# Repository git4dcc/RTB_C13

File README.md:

# RTB_C13

My homebrew RTB C13 track sensor features a 4 channel RailCom® detector, real-time block occupancy monitoring, and dedicated short-circuit protection. It also includes a built-in EDG bus interface, allowing for seamless accessory fan-out and expanded system integration.

<details>
<summary>See also</summary>

- [RTB_C10 - Master](/../../../../git4dcc/RTB_C10)
- [RTB_C11 - Power](/../../../../git4dcc/RTB_C11)
- [RTB_C12 - Booster](/../../../../git4dcc/RTB_C12)

</details>

<details>
<summary>User Guides</summary>

- User Guide - DE
- [User Guide - EN](https://rtb4dcc.de/rtb_user_guide_en/)

</details>

## Track Sensor features
- **HDX**
  - HDX bus (2Mbps half duplex, RS-485 differential)
- **EDG**
  - EDG accessory bus bridge (2Mbps half duplex, TTL level)
- **DCC**
  - Quad-Channel Real-time RailCom® Monitoring and Block Occupancy detection.
  - Current measurement per channel
  - Short-circuit safeguarding for all 4 channels
- **Railcom Detector**
  - channel 1 / channel 2
  - detects unlimited number of decoder per track
  - real-time reporting
- **Current Sensor**
  - 1mA current sensitivity
- firmware update over the bus

# Hardware
The PCB layout uses SMD footprints with 0.4mm pitch, 0603 parts down to 0402. Reflow soldering is mandatory.
The PCB has been optimized for automated assembly (SMD parts are located on bottom side).

## PCB
- 2-layer PCB, FR4, 1.6mm
- CPU: AVR64DB48

## Kicad
[Schematic](doc/C13_schematic.pdf) | [Layout](doc/C13_layout.pdf) | [Gerber](gerber)

# Firmware
Filename structure: { **pcb** }{ **code** }{ **version** }.hex

Example: **C13F0001**.hex

|   | Description |
| --- | --- |
| **pcb** | Name of matching hardware (**C13**) |
| **code** | Type of code contained (**R**=rom, **B**=bootloader, **F**=flash, **U**=bld update, **P**=UPDI factory code) |
| **version** | Release version (**####**) |

[Firmware files](firmware)

## UPDI / Fuses
The fuse settings as well as the P-code (C13Pxxxx.hex) has to be installed by using UPDI.<br>

| Fuses Setting |
| --- |
||

# Images

This project is intended for hobby use only and is distributed in accordance with the Apache License 2.0 agreement.

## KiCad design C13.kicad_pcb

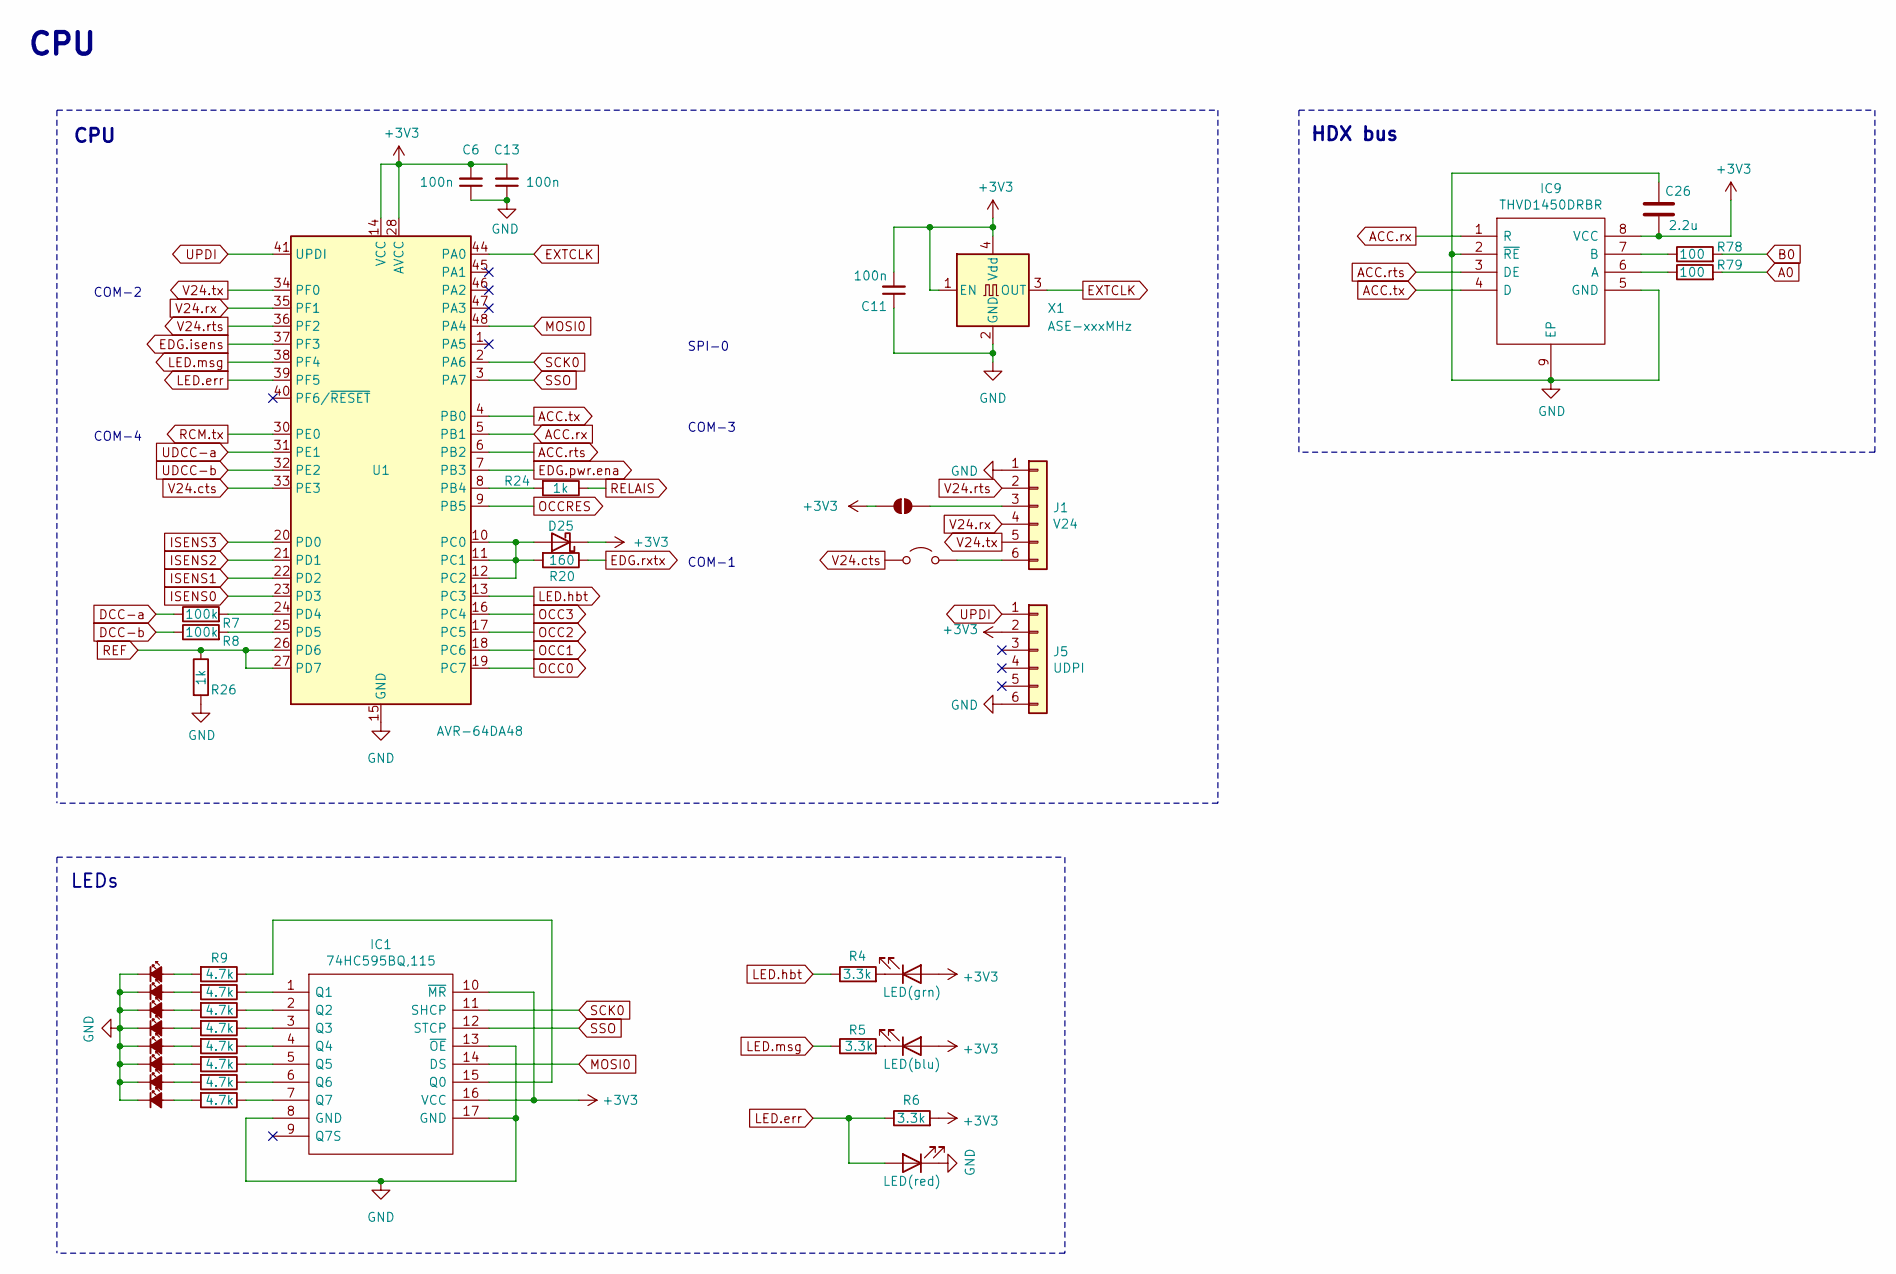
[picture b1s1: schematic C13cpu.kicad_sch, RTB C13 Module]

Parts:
C6, C13: 100n; C_0402_1005Metric; LCSC Part # C307331
C11: 100n; C_0603_1608Metric; LCSC Part # C14663
C26: 2.2u; C_1206_3216Metric; LCSC Part # C50254
D3: LED(grn); LED_0603_1608Metric
D5: LED(blu); LED_0603_1608Metric
D6: LED(red); LED_0603_1608Metric
D7, D8, D9, D10, D11, D12, D13, D14: LED(wht); LED_0603_1608Metric
D25: Schottky; D_0603_1608Metric; LCSC Part # C153761
IC1: 74HC595BQ,115; 74HC595BQ115; Mouser Part Number 771-74HC595BQ-G; LCSC Part # C547123
IC9: THVD1450DRBR; SON65P300X300X100-9N-D; LCSC Part # C1850226
J1: V24; PinHeader_1x06_P2.54mm_Vertical
J5: UDPI; PinHeader_2x03_P1.27mm_Vertical
JP1: SolderJumper_2_Open; SolderJumper-2_P1.3mm_Open_RoundedPad1.0x1.5mm
JP2: Jumper_2_Open; PinHeader_1x02_P2.54mm_Vertical
R4: 3.3k; R_0402_1005Metric; LCSC Part # C25890
R5, R6: 3.3k; R_0603_1608Metric; LCSC Part # C22978
R7, R8: 100k; R_0603_1608Metric; LCSC Part # C25803
R9, R10, R11, R12, R13, R14, R15, R16: 4.7k; R_0603_1608Metric; LCSC Part # C23162
R20: 160; R_0603_1608Metric; LCSC Part # C22808
R24, R26: 1k; R_0402_1005Metric; LCSC Part # C11702
R78, R79: 100; R_1206_3216Metric; LCSC Part # C17901
U1: AVR-64DA48; UQFN-48-1EP_6x6mm_P0.4mm_EP4.62x4.62mm; LCSC Part # C3227372
X1: ASE-xxxMHz; Oscillator_SMD_Abracon_ASE-4Pin_3.2x2.5mm; LCSC Part # C1987527

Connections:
+3V3: C6.2, C11.2, C13.2, C26.2, D3.2 (A), D5.2 (A), D25.1 (K), IC1.10 (~MR), IC1.16 (VCC), IC9.8 (VCC), J5.2, JP1.2 (B), R6.2, U1.14 (VCC), U1.28 (AVCC), U1.42 (VCC), X1.1 (EN), X1.4 (Vdd); also elsewhere on the board
A0: R79.2; also elsewhere on the board
ACC.rts: IC9.3 (DE), U1.6 (PB2)
ACC.rx: IC9.1 (R), U1.5 (PB1)
ACC.tx: IC9.4 (D), U1.4 (PB0)
B0: R78.2; also elsewhere on the board
DCC-a: R7.1; also elsewhere on the board
DCC-b: R8.1; also elsewhere on the board
EDG.isens: U1.37 (PF3); also elsewhere on the board
EDG.pwr.ena: U1.7 (PB3); also elsewhere on the board
EDG.rxtx: R20.1; also elsewhere on the board
EXTCLK: U1.44 (PA0), X1.3 (OUT)
GND: C6.1, C11.1, C13.1, C26.1, D6.1 (K), D7.1 (K), D8.1 (K), D9.1 (K), D10.1 (K), D11.1 (K), D12.1 (K), D13.1 (K), D14.1 (K), IC1.8 (GND), IC1.13 (~OE), IC1.17 (GND), IC9.2 (~RE), IC9.5 (GND), IC9.9 (EP), J1.1, J5.6, R26.2, U1.15 (GND), U1.29 (GND), U1.43 (GND), U1.49 (GND), X1.2 (GND); also elsewhere on the board
ISENS0: U1.23 (PD3); also elsewhere on the board
ISENS1: U1.22 (PD2); also elsewhere on the board
ISENS2: U1.21 (PD1); also elsewhere on the board
ISENS3: U1.20 (PD0); also elsewhere on the board
LED.err: D6.2 (A), R6.1, U1.39 (PF5)
LED.hbt: R4.1, U1.13 (PC3)
LED.msg: R5.1, U1.38 (PF4)
MOSI0: IC1.14 (DS), U1.48 (PA4)
unnamed: D3.1 (K), R4.2
unnamed: D5.1 (K), R5.2
unnamed: D7.2 (A), R16.2
unnamed: D8.2 (A), R15.2
unnamed: D9.2 (A), R14.2
unnamed: D10.2 (A), R13.2
unnamed: D11.2 (A), R12.2
unnamed: D12.2 (A), R11.2
unnamed: D13.2 (A), R10.2
unnamed: D14.2 (A), R9.2
unnamed: D25.2 (A), R20.2, U1.10 (PC0), U1.11 (PC1), U1.12 (PC2)
unnamed: IC1.15 (Q0), R9.1
unnamed: IC1.1 (Q1), R10.1
unnamed: IC1.2 (Q2), R11.1
unnamed: IC1.3 (Q3), R12.1
unnamed: IC1.4 (Q4), R13.1
unnamed: IC1.5 (Q5), R14.1
unnamed: IC1.6 (Q6), R15.1
unnamed: IC1.7 (Q7), R16.1
unnamed: IC9.6 (A), R79.1
unnamed: IC9.7 (B), R78.1
unnamed: J1.3, JP1.1 (A)
unnamed: J1.6, JP2.1 (A)
unnamed: R24.2, U1.8 (PB4)
OCC0: U1.19 (PC7); also elsewhere on the board
OCC1: U1.18 (PC6); also elsewhere on the board
OCC2: U1.17 (PC5); also elsewhere on the board
OCC3: U1.16 (PC4); also elsewhere on the board
OCCRES: U1.9 (PB5); also elsewhere on the board
PD4: R7.2, U1.24 (PD4); also elsewhere on the board
PD5: R8.2, U1.25 (PD5); also elsewhere on the board
RCM.tx: U1.30 (PE0); also elsewhere on the board
REF: R26.1, U1.26 (PD6), U1.27 (PD7); also elsewhere on the board
RELAIS: R24.1; also elsewhere on the board
SCK0: IC1.11 (SHCP), U1.2 (PA6)
SSO: IC1.12 (STCP), U1.3 (PA7)
UDCC-a: U1.31 (PE1); also elsewhere on the board
UDCC-b: U1.32 (PE2); also elsewhere on the board
UPDI: J5.1, U1.41 (UPDI)
V24.cts: JP2.2 (B), U1.33 (PE3)
V24.rts: J1.2, U1.36 (PF2)
V24.rx: J1.4, U1.35 (PF1)
V24.tx: J1.5, U1.34 (PF0)

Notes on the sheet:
COM-4
COM-1
COM-3
CPU
COM-2
LEDs
SPI-0
HDX bus

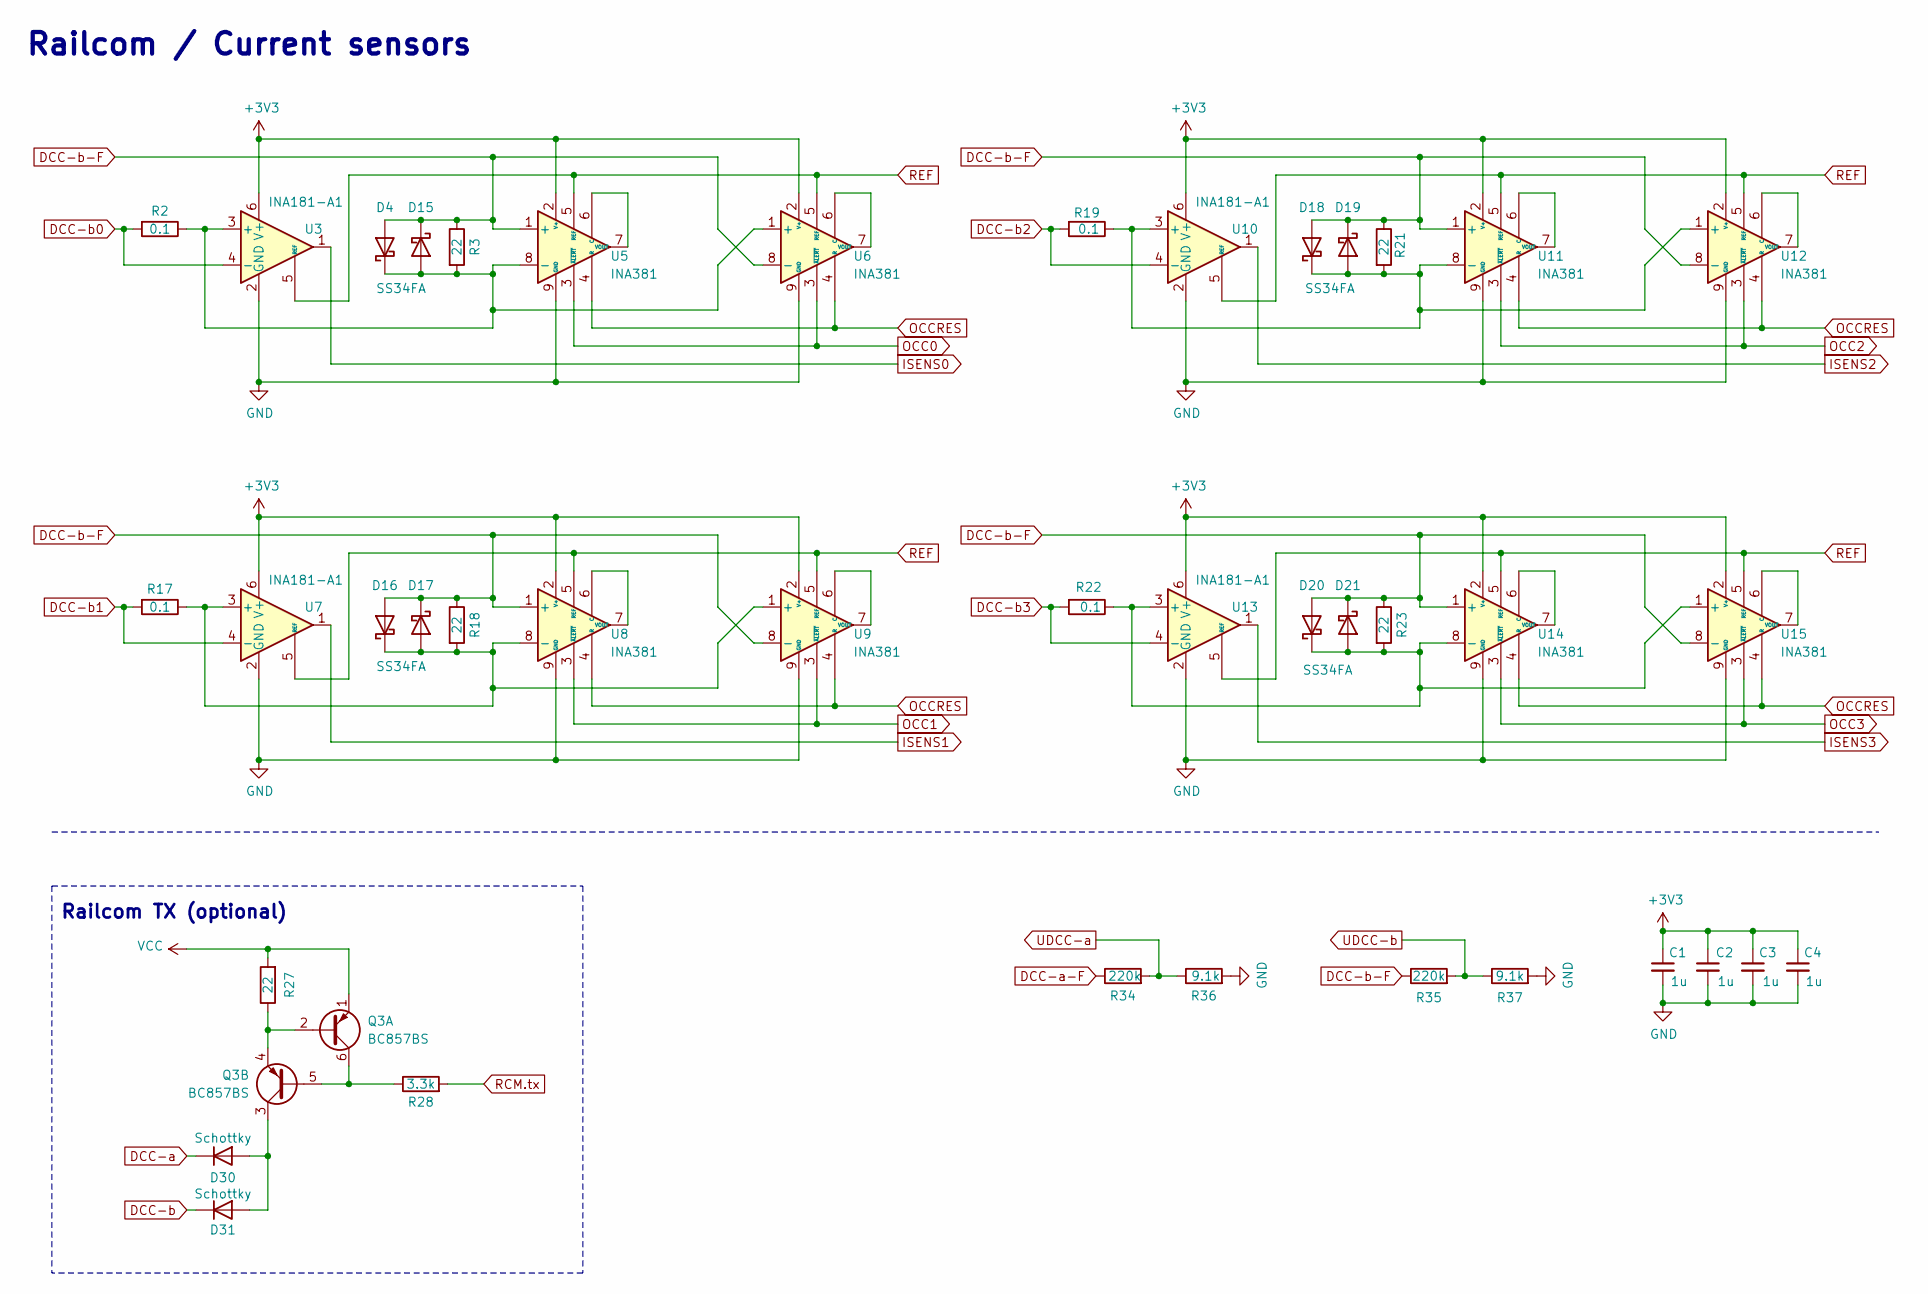
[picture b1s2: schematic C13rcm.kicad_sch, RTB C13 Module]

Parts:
C1, C2, C3, C4: 1u; C_0805_2012Metric; LCSC Part # C28323
D4, D15, D16, D17, D18, D19, D20, D21: SS34FA; D_SOD-123F; LCSC Part # C84632
D30, D31: Schottky; D_0603_1608Metric; LCSC Part # C153761
Q3: BC857BS; SOT-363_SC-70-6; LCSC Part # C156320
R2, R17, R19, R22: 0.1; R_1206_3216Metric; LCSC Part # C188071
R3, R18, R21, R23, R27: 22; R_0603_1608Metric; LCSC Part # C23345
R28: 3.3k; R_0603_1608Metric; LCSC Part # C22978
R34, R35: 220k; R_0603_1608Metric; LCSC Part # C22961
R36, R37: 9.1k; R_0603_1608Metric; LCSC Part # C23260
U3, U7, U10, U13: INA181-A1; SOT-23-6; LCSC Part # C2058943
U5, U6, U8, U9, U11, U12, U14, U15: INA381; WSON-8-1EP_2x2mm_P0.5mm_EP0.9x1.6mm; LCSC Part # C544574

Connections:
+3V3: C1.1, C2.1, C3.1, C4.1, Q3.1 (E1), R27.2, U3.6 (V+), U5.2 (V+), U6.2 (V+), U7.6 (V+), U8.2 (V+), U9.2 (V+), U10.6 (V+), U11.2 (V+), U12.2 (V+), U13.6 (V+), U14.2 (V+), U15.2 (V+); also elsewhere on the board
DCC-a: D30.1 (K); also elsewhere on the board
DCC-a-F: R34.1; also elsewhere on the board
DCC-b: D31.1 (K); also elsewhere on the board
DCC-b0: R2.2, U3.4 (-); also elsewhere on the board
DCC-b1: R17.2, U7.4 (-); also elsewhere on the board
DCC-b2: R19.2, U10.4 (-); also elsewhere on the board
DCC-b3: R22.2, U13.4 (-); also elsewhere on the board
DCC-b-F: D4.2 (A), D15.1 (K), D16.2 (A), D17.1 (K), D18.2 (A), D19.1 (K), D20.2 (A), D21.1 (K), R3.1, R18.1, R21.1, R23.1, R35.1, U5.1 (+), U6.8 (-), U8.1 (+), U9.8 (-), U11.1 (+), U12.8 (-), U14.1 (+), U15.8 (-); also elsewhere on the board
GND: C1.2, C2.2, C3.2, C4.2, R36.2, R37.2, U3.2 (GND), U5.9 (GND), U6.9 (GND), U7.2 (GND), U8.9 (GND), U9.9 (GND), U10.2 (GND), U11.9 (GND), U12.9 (GND), U13.2 (GND), U14.9 (GND), U15.9 (GND); also elsewhere on the board
ISENS0: U3.1; also elsewhere on the board
ISENS1: U7.1; also elsewhere on the board
ISENS2: U10.1; also elsewhere on the board
ISENS3: U13.1; also elsewhere on the board
unnamed: D4.1 (K), D15.2 (A), R2.1, R3.2, U3.3 (+), U5.8 (-), U6.1 (+)
unnamed: D16.1 (K), D17.2 (A), R17.1, R18.2, U7.3 (+), U8.8 (-), U9.1 (+)
unnamed: D18.1 (K), D19.2 (A), R19.1, R21.2, U10.3 (+), U11.8 (-), U12.1 (+)
unnamed: D20.1 (K), D21.2 (A), R22.1, R23.2, U13.3 (+), U14.8 (-), U15.1 (+)
unnamed: D30.2 (A), D31.2 (A), Q3.3 (C2)
unnamed: Q3.2 (B1), Q3.4 (E2), R27.1
unnamed: Q3.5 (B2), Q3.6 (C1), R28.1
unnamed: U5.6 (C), U5.7 (VOUT)
unnamed: U6.6 (C), U6.7 (VOUT)
unnamed: U8.6 (C), U8.7 (VOUT)
unnamed: U9.6 (C), U9.7 (VOUT)
unnamed: U11.6 (C), U11.7 (VOUT)
unnamed: U12.6 (C), U12.7 (VOUT)
unnamed: U14.6 (C), U14.7 (VOUT)
unnamed: U15.6 (C), U15.7 (VOUT)
OCC0: U5.3 (~ALERT), U6.3 (~ALERT); also elsewhere on the board
OCC1: U8.3 (~ALERT), U9.3 (~ALERT); also elsewhere on the board
OCC2: U11.3 (~ALERT), U12.3 (~ALERT); also elsewhere on the board
OCC3: U14.3 (~ALERT), U15.3 (~ALERT); also elsewhere on the board
OCCRES: U5.4 (R), U6.4 (R), U8.4 (R), U9.4 (R), U11.4 (R), U12.4 (R), U14.4 (R), U15.4 (R); also elsewhere on the board
RCM.tx: R28.2; also elsewhere on the board
REF: U3.5 (REF), U5.5 (REF), U6.5 (REF), U7.5 (REF), U8.5 (REF), U9.5 (REF), U10.5 (REF), U11.5 (REF), U12.5 (REF), U13.5 (REF), U14.5 (REF), U15.5 (REF); also elsewhere on the board
UDCC-a: R34.2, R36.1; also elsewhere on the board
UDCC-b: R35.2, R37.1; also elsewhere on the board

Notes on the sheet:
Railcom / Current sensors
Railcom TX (optional)

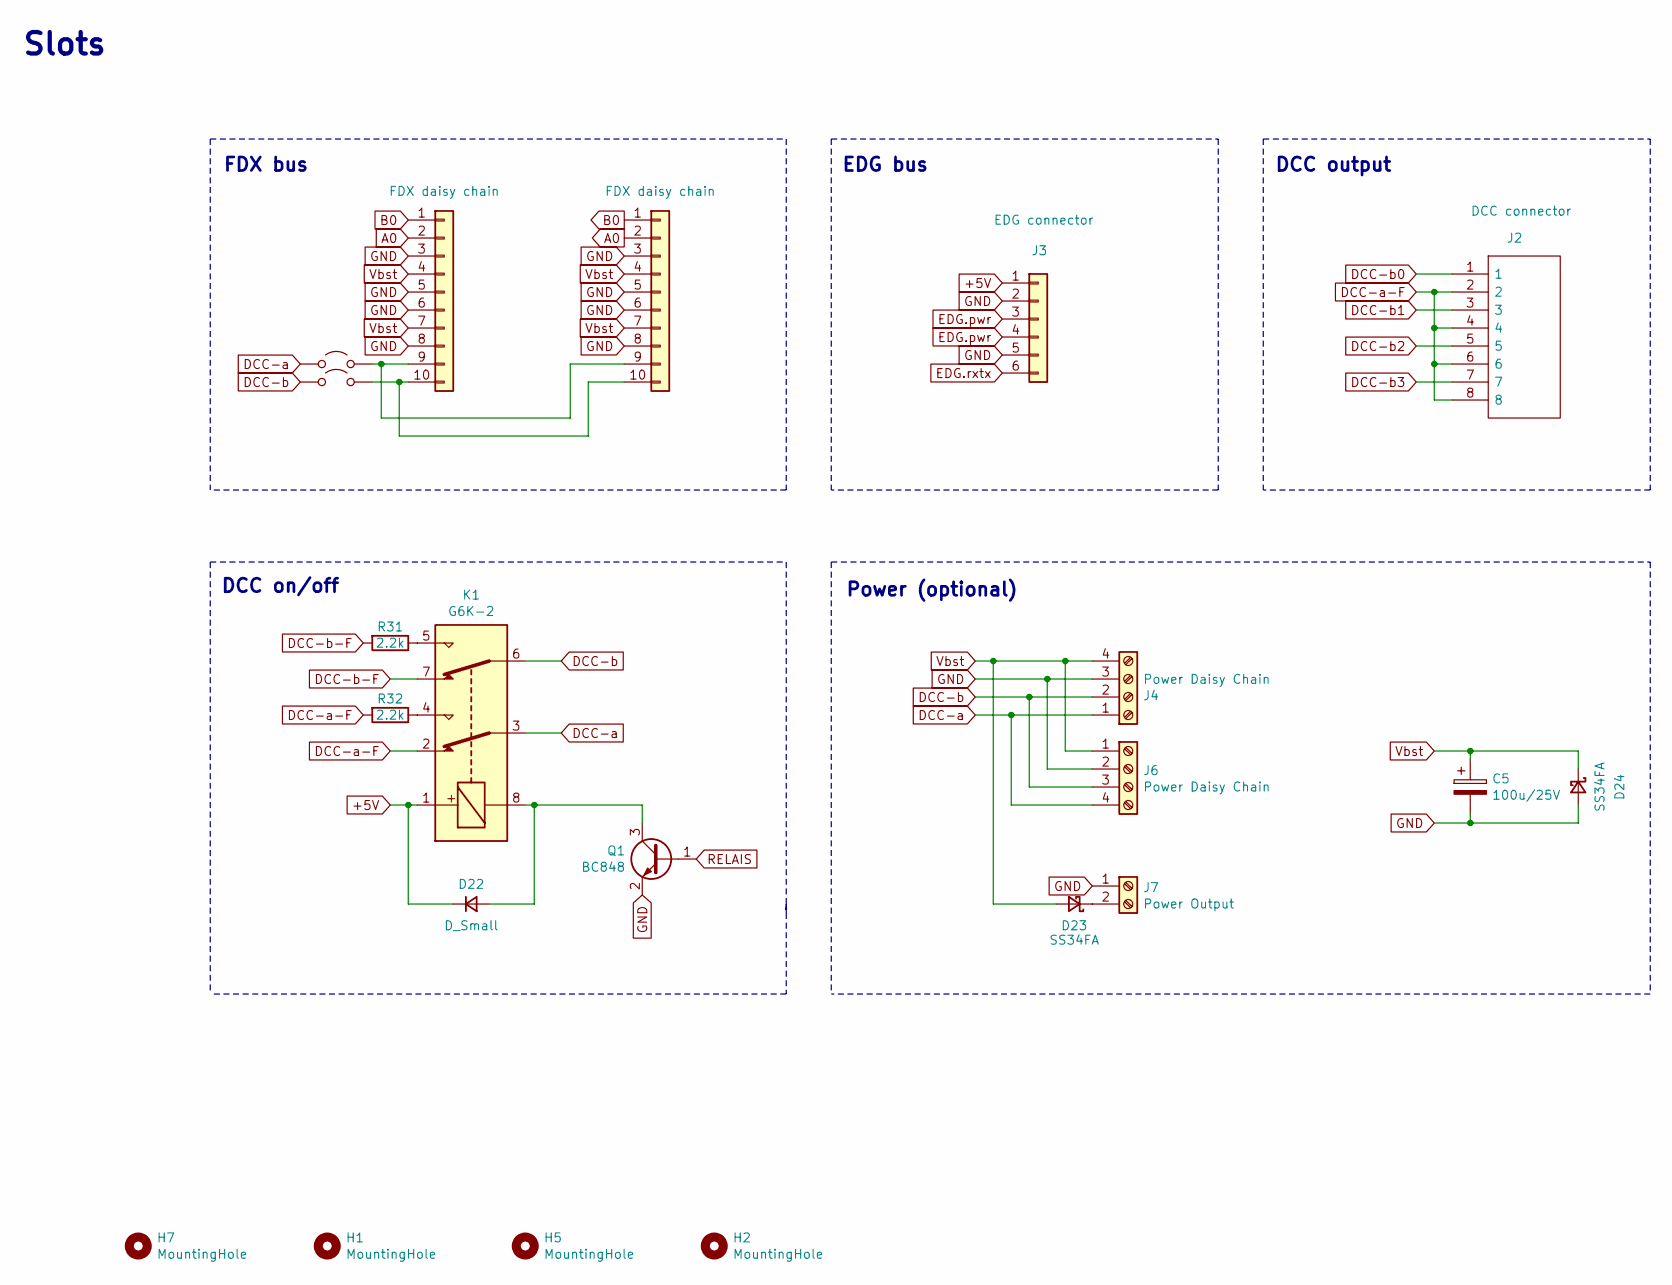
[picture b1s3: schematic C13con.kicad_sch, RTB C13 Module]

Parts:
C5: 100u/25V; CP_Radial_D6.3mm_P2.50mm
C.0.0, C.0.1: FDX daisy chain; IDC-Header_2x05_P2.54mm_Vertical
D22: D_Small; D_SOD-323; LCSC Part # C191023
D23, D24: SS34FA; D_SOD-123F; LCSC Part # C84632
H1, H2, H5, H7: MountingHole; MountingHole_3.2mm_M3_ISO7380_Pad
J2: DCC connector; 1725711
J3: EDG connector; IDC-Header_2x03_P2.54mm_Vertical
J4, J6: Power Daisy Chain; 1725672
J7: Power Output; 1725656
JP3, JP4: Jumper_2_Open; PinHeader_1x02_P2.54mm_Vertical
K1: G6K-2; Relay_DPDT_Omron_G6K-2F-Y
Q1: BC848; SOT-323_SC-70; LCSC Part # C600677
R31, R32: 2.2k; R_0603_1608Metric; LCSC Part # C4190

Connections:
+5V: D22.1 (K), J3.1, K1.1; also elsewhere on the board
A0: C.0.0.2, C.0.1.2; also elsewhere on the board
B0: C.0.0.1, C.0.1.1; also elsewhere on the board
DCC-a: J4.1, J6.4, JP3.2 (B), K1.3; also elsewhere on the board
DCC-a-F: J2.2, J2.4, J2.6, J2.8, K1.2, R32.2; also elsewhere on the board
DCC-b: J4.2, J6.3, JP4.2 (B), K1.6; also elsewhere on the board
DCC-b0: J2.1; also elsewhere on the board
DCC-b1: J2.3; also elsewhere on the board
DCC-b2: J2.5; also elsewhere on the board
DCC-b3: J2.7; also elsewhere on the board
DCC-b-F: K1.7, R31.2; also elsewhere on the board
EDG.pwr: J3.3, J3.4; also elsewhere on the board
EDG.rxtx: J3.6; also elsewhere on the board
GND: C5.2, C.0.0.3, C.0.0.5, C.0.0.6, C.0.0.8, C.0.1.3, C.0.1.5, C.0.1.6, C.0.1.8, D24.2 (A), J3.2, J3.5, J4.3, J6.2, J7.1, Q1.2 (E); also elsewhere on the board
unnamed: C.0.0.9, C.0.1.9, JP3.1 (A)
unnamed: C.0.0.10, C.0.1.10, JP4.1 (A)
unnamed: D22.2 (A), K1.8, Q1.3 (C)
unnamed: D23.1 (K), J7.2
unnamed: K1.4, R32.1
unnamed: K1.5, R31.1
RELAIS: Q1.1 (B); also elsewhere on the board
Vbst: C5.1, C.0.0.4, C.0.0.7, C.0.1.4, C.0.1.7, D23.2 (A), D24.1 (K), J4.4, J6.1; also elsewhere on the board

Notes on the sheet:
Power (optional)
EDG bus
DCC output
FDX bus
Slots
DCC on/off

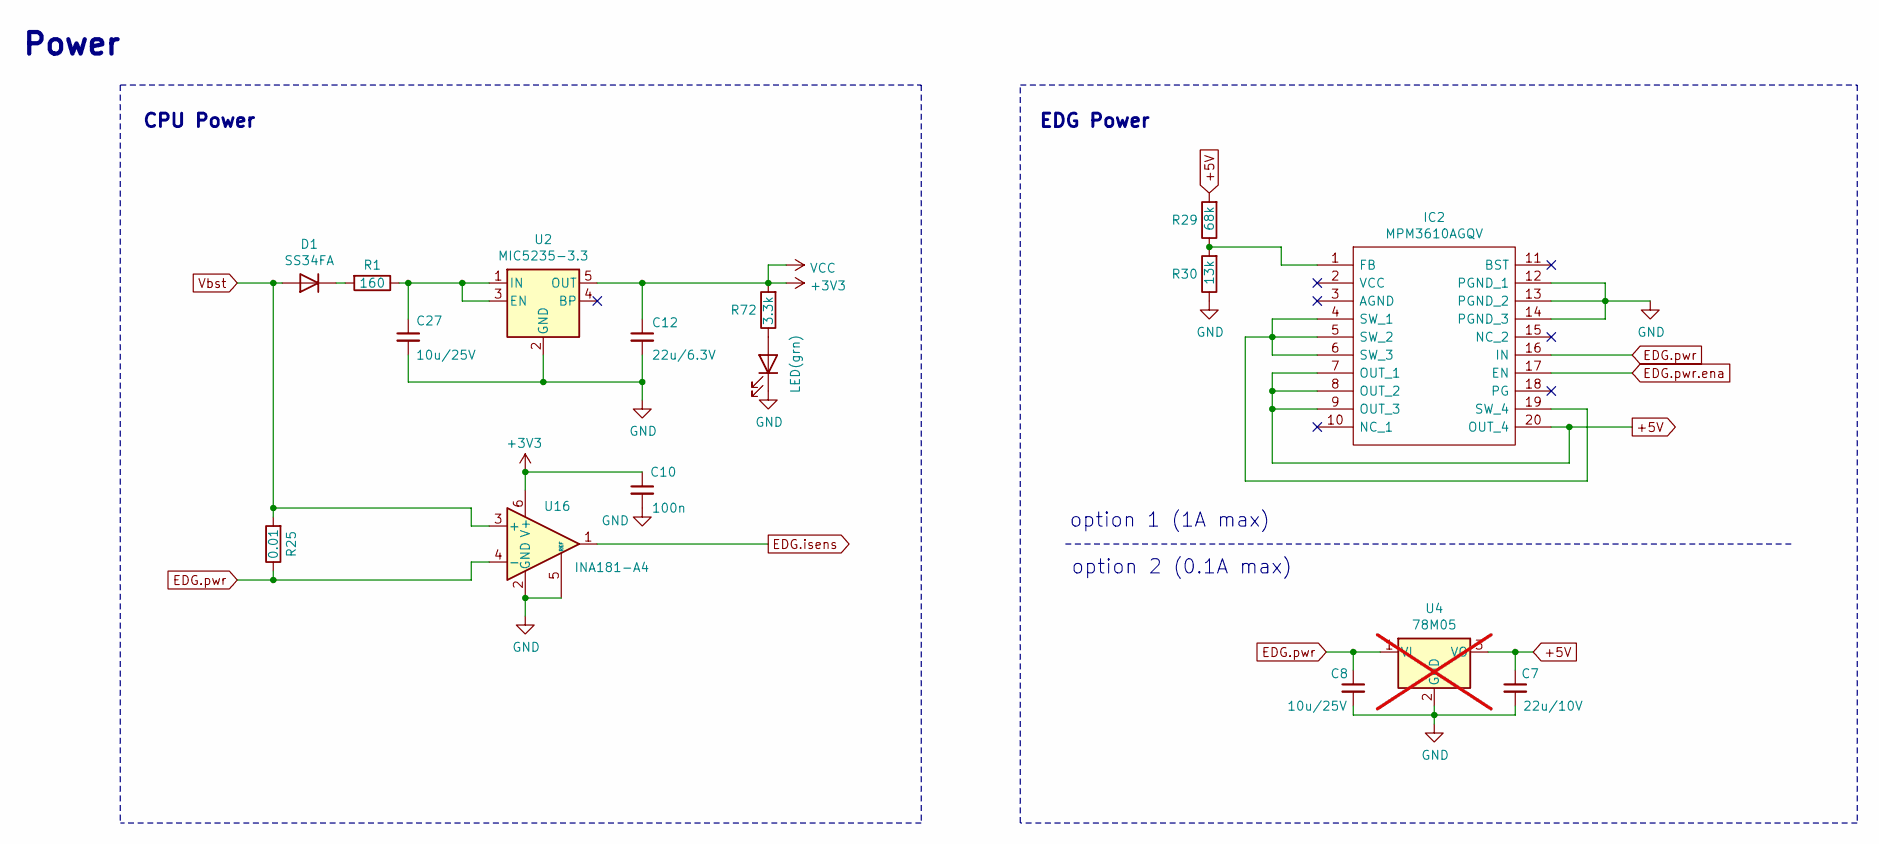
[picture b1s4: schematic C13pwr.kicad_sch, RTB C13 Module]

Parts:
C7: 22u/10V; C_1206_3216Metric; LCSC Part # C12891
C8: 10u/25V; C_1206_3216Metric; LCSC Part # C13585
C10: 100n; C_0402_1005Metric; LCSC Part # C1525
C12: 22u/6.3V; C_0805_2012Metric; LCSC Part # C45783
C27: 10u/25V; C_0805_2012Metric; LCSC Part # C440198
D1: SS34FA; D_SOD-123F; LCSC Part # C84632
D2: LED(grn); LED_0603_1608Metric
IC2: MPM3610AGQV; MPM3610AGQVP; LCSC Part # C5173872
R1: 160; R_0805_2012Metric; LCSC Part # C17471
R25: 0.01; R_1206_3216Metric; LCSC Part # C308574
R29: 68k; R_0402_1005Metric; LCSC Part # C36871
R30: 13k; R_0402_1005Metric; LCSC Part # C25754
R72: 3.3k; R_0603_1608Metric; LCSC Part # C22978
U2: MIC5235-3.3; SOT-23-5; LCSC Part # C89886
U4: 78M05; TO-252-2; not fitted
U16: INA181-A4; SOT-23-6; LCSC Part # C2058842

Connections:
+3V3: C10.1, C12.1, R72.2, U2.5 (OUT), U16.6 (V+); also elsewhere on the board
+5V: C7.1, IC2.7 (OUT_1), IC2.8 (OUT_2), IC2.9 (OUT_3), IC2.20 (OUT_4), R29.2, U4.3 (VO); also elsewhere on the board
EDG.isens: U16.1; also elsewhere on the board
EDG.pwr: C8.1, IC2.16 (IN), R25.1, U4.1 (VI), U16.4 (-); also elsewhere on the board
EDG.pwr.ena: IC2.17 (EN); also elsewhere on the board
GND: C7.2, C8.2, C10.2, C12.2, C27.2, D2.1 (K), IC2.12 (PGND_1), IC2.13 (PGND_2), IC2.14 (PGND_3), R30.1, U2.2 (GND), U4.2 (GND), U16.2 (GND), U16.5 (REF); also elsewhere on the board
unnamed: D1.1 (K), R1.2
unnamed: D2.2 (A), R72.1
unnamed: IC2.1 (FB), R29.1, R30.2
unnamed: IC2.4 (SW_1), IC2.5 (SW_2), IC2.6 (SW_3), IC2.19 (SW_4)
unnamed: C27.1, R1.1, U2.1 (IN), U2.3 (EN)
Vbst: D1.2 (A), R25.2, U16.3 (+); also elsewhere on the board

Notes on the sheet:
EDG Power
option 1 (1A max)
option 2 (0.1A max)
Power
CPU Power

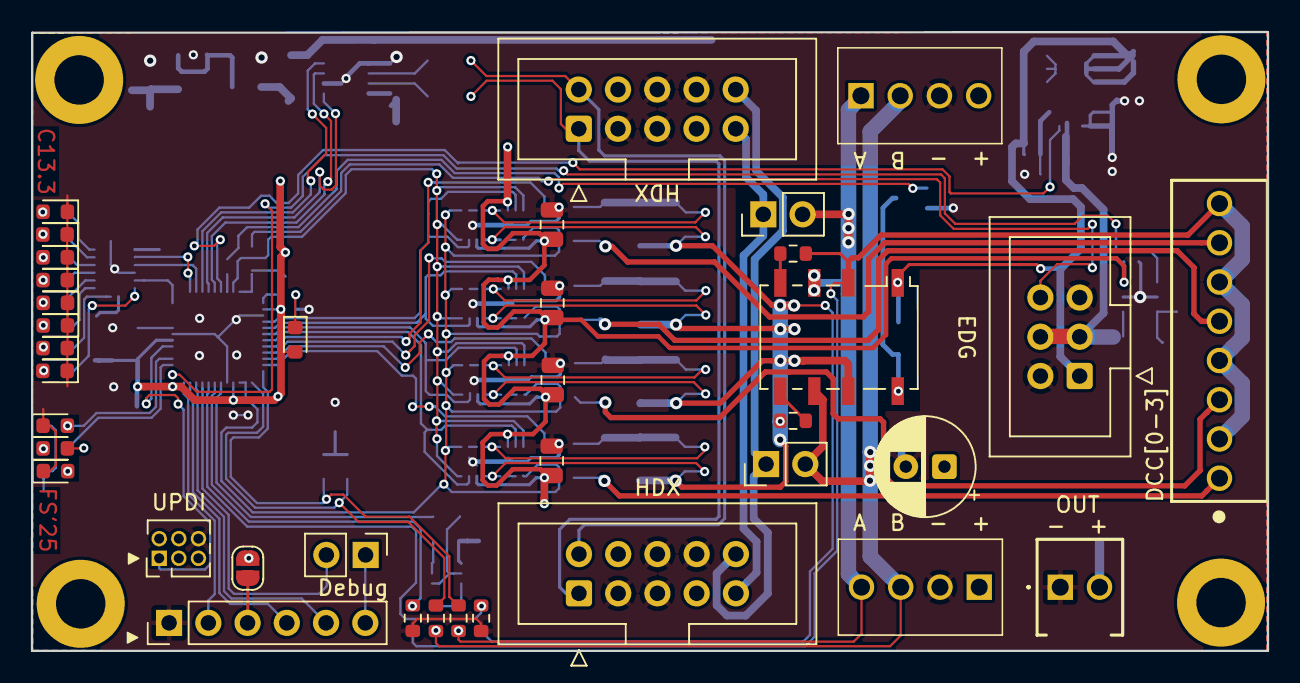
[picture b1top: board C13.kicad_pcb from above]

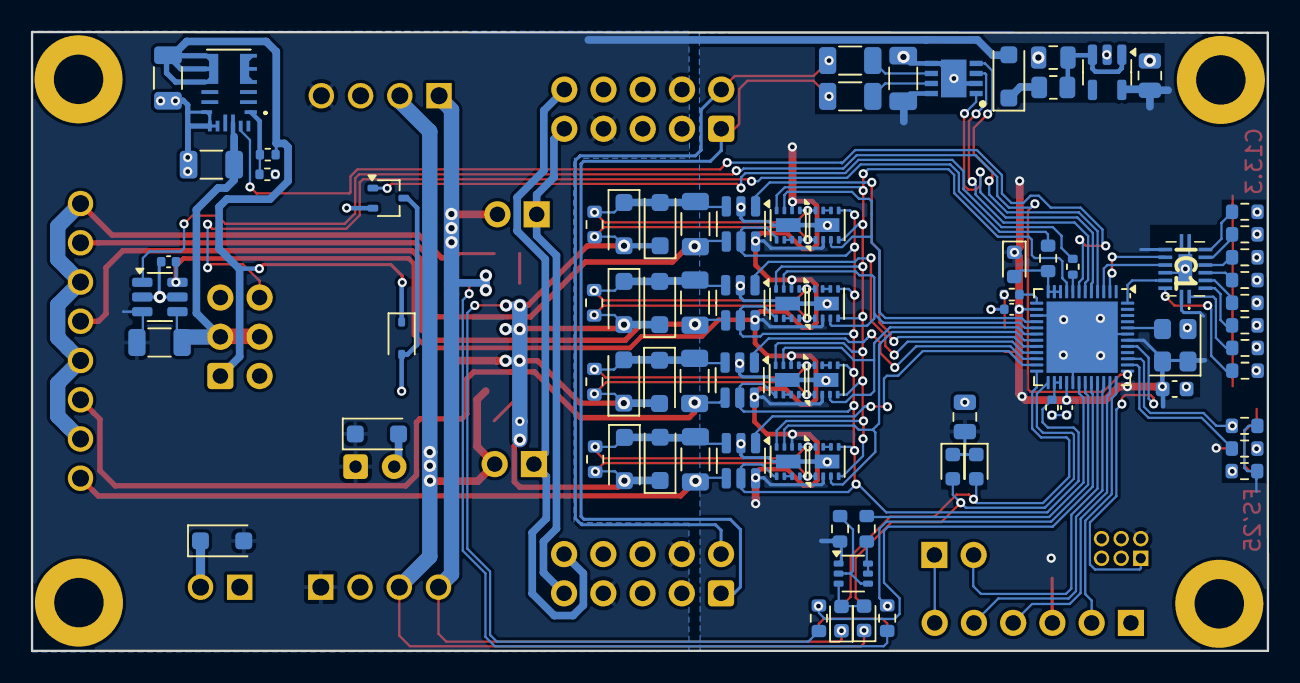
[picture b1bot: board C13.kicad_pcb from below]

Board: 2 copper layers, 80.0 x 40.1 mm, 122 parts (85 on the bottom side), 99 nets.

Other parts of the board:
C9: 1u; C_0805_2012Metric
D26, D27: Schottky; D_0603_1608Metric

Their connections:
+3V3: C9.1, D26.1 (K), D27.1 (K); also elsewhere on the board
GND: C9.2; also elsewhere on the board
PD4: D27.2 (A); also elsewhere on the board
PD5: D26.2 (A); also elsewhere on the board

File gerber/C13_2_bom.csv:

"Designator","Qty","Value","Exclude from BOM","Footprint","LCSC Part #"
"C.0.0,C.0.1","2","FDX daisy chain","Excluded from BOM","Connector_IDC:IDC-Header_2x05_P2.54mm_Vertical",""
"C5","1","100u/25V","Excluded from BOM","Capacitor_THT:CP_Radial_D6.3mm_P2.50mm",""
"D2,D3","2","LED(grn)","Excluded from BOM","LED_SMD:LED_0603_1608Metric",""
"D5","1","LED(blu)","Excluded from BOM","LED_SMD:LED_0603_1608Metric",""
"D6","1","LED(red)","Excluded from BOM","LED_SMD:LED_0603_1608Metric",""
"D7,D8,D9,D10,D11,D12,D13,D14","8","LED(wht)","Excluded from BOM","LED_SMD:LED_0603_1608Metric",""
"H1,H2,H5,H7","4","MountingHole","Excluded from BOM","MountingHole:MountingHole_3.2mm_M3_ISO7380_Pad",""
"J1","1","V24","Excluded from BOM","Connector_PinHeader_2.54mm:PinHeader_1x06_P2.54mm_Vertical",""
"J2","1","DCC connector","Excluded from BOM","RTB:1725711",""
"J3","1","EDG connector","Excluded from BOM","Connector_IDC:IDC-Header_2x03_P2.54mm_Vertical",""
"J4,J6","2","Power Daisy Chain","Excluded from BOM","RTB:1725672",""
"J5","1","UDPI","Excluded from BOM","Connector_PinHeader_1.27mm:PinHeader_2x03_P1.27mm_Vertical",""
"J7","1","Power Output","Excluded from BOM","RTB:1725656",""
"JP1","1","SolderJumper_2_Open","Excluded from BOM","Jumper:SolderJumper-2_P1.3mm_Open_RoundedPad1.0x1.5mm",""
"JP2,JP3,JP4","3","Jumper_2_Open","Excluded from BOM","Connector_PinHeader_2.54mm:PinHeader_1x02_P2.54mm_Vertical",""
"K1","1","G6K-2","Excluded from BOM","Relay_SMD:Relay_DPDT_Omron_G6K-2F-Y",""
"U4","1","78M05","Excluded from BOM","Package_TO_SOT_SMD:TO-252-2",""
"C10","1","100n","","Capacitor_SMD:C_0402_1005Metric","C1525"
"R31,R32","2","2.2k","","Resistor_SMD:R_0603_1608Metric","C4190"
"R24,R26","2","1k","","Resistor_SMD:R_0402_1005Metric","C11702"
"C7","1","22u/10V","","Capacitor_SMD:C_1206_3216Metric","C12891"
"C8","1","10u/25V","","Capacitor_SMD:C_1206_3216Metric","C13585"
"C11","1","100n","","Capacitor_SMD:C_0603_1608Metric","C14663"
"R1","1","160","","Resistor_SMD:R_0805_2012Metric","C17471"
"R78,R79","2","100","","Resistor_SMD:R_1206_3216Metric","C17901"
"R20","1","160","","Resistor_SMD:R_0603_1608Metric","C22808"
"R34,R35","2","220k","","Resistor_SMD:R_0603_1608Metric","C22961"
"R5,R6,R28,R72","4","3.3k","","Resistor_SMD:R_0603_1608Metric","C22978"
"R9,R10,R11,R12,R13,R14,R15,R16","8","4.7k","","Resistor_SMD:R_0603_1608Metric","C23162"
"R36,R37","2","9.1k","","Resistor_SMD:R_0603_1608Metric","C23260"
"R3,R18,R21,R23,R27","5","22","","Resistor_SMD:R_0603_1608Metric","C23345"
"R30","1","13k","","Resistor_SMD:R_0402_1005Metric","C25754"
"R7,R8","2","100k","","Resistor_SMD:R_0603_1608Metric","C25803"
"R4","1","3.3k","","Resistor_SMD:R_0402_1005Metric","C25890"
"C1,C2,C3,C4","4","1u","","Capacitor_SMD:C_0805_2012Metric","C28323"
"R29","1","68k","","Resistor_SMD:R_0402_1005Metric","C36871"
"C12","1","22u/6.3V","","Capacitor_SMD:C_0805_2012Metric","C45783"
"C26","1","2.2u","","Capacitor_SMD:C_1206_3216Metric","C50254"
"D1,D4,D15,D16,D17,D18,D19,D20,D21,D23,D24","11","SS34FA","","Diode_SMD:D_SOD-123F","C84632"
"U2","1","MIC5235-3.3","","Package_TO_SOT_SMD:SOT-23-5","C89886"
"D25,D30,D31","3","Schottky","","Diode_SMD:D_0603_1608Metric","C153761"
"Q3","1","BC857BS","","Package_TO_SOT_SMD:SOT-363_SC-70-6","C156320"
"R2,R17,R19,R22","4","0.1","","Resistor_SMD:R_1206_3216Metric","C188071"
"D22","1","D_Small","","Diode_SMD:D_SOD-323","C191023"
"C6,C13","2","100n","","Capacitor_SMD:C_0402_1005Metric","C307331"
"R25","1","0.01","","Resistor_SMD:R_1206_3216Metric","C308574"
"C27","1","10u/25V","","Capacitor_SMD:C_0805_2012Metric","C440198"
"U5,U6,U8,U9,U11,U12,U14,U15","8","INA381","","Package_SON:WSON-8-1EP_2x2mm_P0.5mm_EP0.9x1.6mm","C544574"
"IC1","1","74HC595BQ,115","","74HC595BQ115","C547123"
"Q1","1","BC848","","Package_TO_SOT_SMD:SOT-323_SC-70","C600677"
"IC9","1","THVD1450DRBR","","RTB:SON65P300X300X100-9N-D","C1850226"
"X1","1","ASE-xxxMHz","","Oscillator:Oscillator_SMD_Abracon_ASE-4Pin_3.2x2.5mm","C1987527"
"U16","1","INA181-A4","","Package_TO_SOT_SMD:SOT-23-6","C2058842"
"U3,U7,U10,U13","4","INA181-A1","","Package_TO_SOT_SMD:SOT-23-6","C2058943"
"U1","1","AVR-64DA48","","Package_DFN_QFN:UQFN-48-1EP_6x6mm_P0.4mm_EP4.62x4.62mm","C3227372"
"IC2","1","MPM3610AGQV","","RTB:MPM3610AGQVP","C5173872"

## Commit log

2025-10-13 mod: conversion to KiCad 9
2025-11-18 mod: part #
2025-11-18 add: fuses document
2025-11-18 Add UPDI / Fuses section to README
    Added UPDI / Fuses section with fuse settings information.
2026-02-20 Change RTB project links to relative paths
    Updated links to relative paths for RTB projects.
2026-02-20 git mirror test
